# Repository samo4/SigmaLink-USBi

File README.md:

# SigmaLink USBi

The SigmaLink USBi is an all-in-one real-time programming interface.

## Testing

- [x] draws less than 500mA
- [ ] why female connector?
- [ ] _too little bulk capacitance on VBUS_ (100u at least)
- [ ] missing pullup on SDA
- [ ] wrong footprint 74LVC2G66
- [ ] wrong footprint B5819W SL
- [ ] Y1 has DNP?
- [ ] _missing pull up on I2C SDA line_
- [x] works with SigmaStudio aftter adding capacitance and pullup on SDA

## Original info

MAIN COORDINATOR: [Max Chan](https://github.com/xcvista)

The SigmaLink USBi is a low-budget real-time programming device for the freeDSP and other DSP boards from Analog Devices. It is a new PCB design based on a CY7C68013 chip.

It has the same features as the Analog Devices USB interface (EVAL-ADUSB2EBZ), such as changing parameters while already using the freeDSP or easy changes of the schematic in SigmaStudio. You also can write your program to the EEPROM.

Please refer to the documentation for more information:

[Google Doc](https://docs.google.com/document/d/13BDac6Mss2I0CBOsSrk4YG-c8GQUpgU41vkwsMnYBss/edit?usp=sharing)

## License

This work and all other materials under https://github.com/freeDSP are licensed under a [Creative Commons Attribution Share-Alike 4.0 license](LICENSE.md). This allows for both personal and commercial derivative works, as long as they credit freeDSP and release their designs under the same license.

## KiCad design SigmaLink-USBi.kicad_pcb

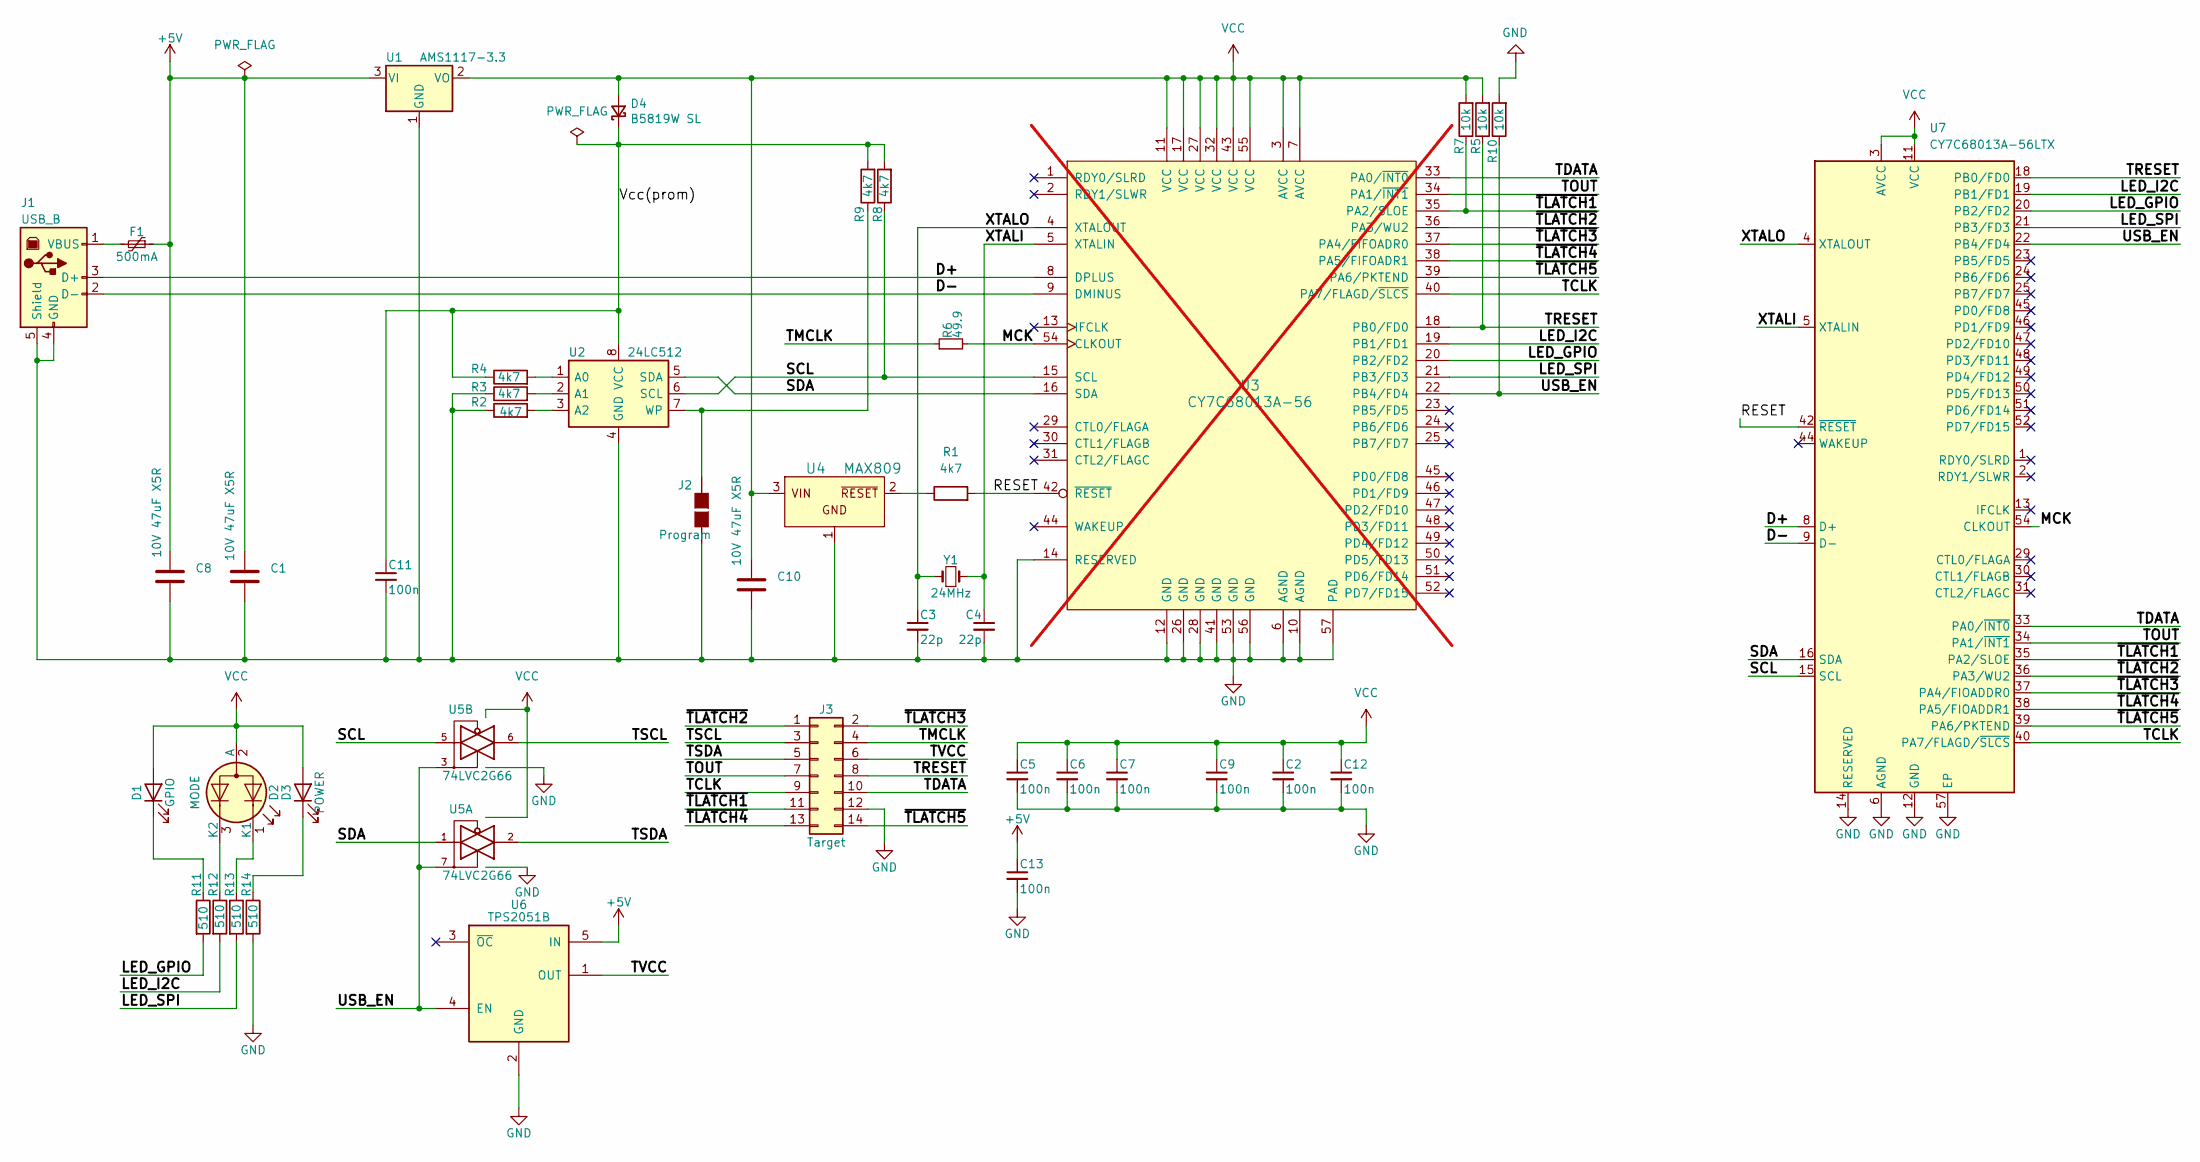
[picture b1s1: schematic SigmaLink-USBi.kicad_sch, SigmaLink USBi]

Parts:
C1, C8, C10: 10V 47uF X5R; C_1206_3216Metric; LCSC C96123
C2, C5, C6, C7, C9, C11, C12, C13: 100n; C_0402_1005Metric; LCSC C1525
C3, C4: 22p; C_0603_1608Metric; LCSC C1653
D1: GPIO; LED_D3.0mm; LCSC C86881
D2: MODE; LED_D3.0mm-3; LCSC C13559
D3: POWER; LED_D3.0mm; LCSC C85160
D4: B5819W SL; D_SOD-123; LCSC C8598
F1: 500mA; Fuse_1812_4532Metric_Pad1.30x3.40mm_HandSolder; LCSC C20979
J1: USB_B; USB_B_OST_USB-B1HSxx_Horizontal; LCSC C46392
J2: Program; PinHeader_1x02_P2.54mm_Vertical
J3: Target; IDC-Header_2x07_P2.54mm_Horizontal; LCSC C146622
R1, R2, R3, R4, R8, R9: 4k7; R_0402_1005Metric; LCSC C25900
R5, R7, R10: 10k; R_0402_1005Metric; LCSC C25744
R6: 49.9; R_0402_1005Metric
R11, R12, R13, R14: 510; R_0402_1005Metric; LCSC 0402
U1: AMS1117-3.3; SOT-223-3_TabPin2; LCSC C6186
U2: 24LC512; SOIC-8_3.9x4.9mm_P1.27mm; LCSC C6487
U3: CY7C68013A-56; QFN-56-1EP_8x8mm_P0.5mm_EP4.6x5.3mm; LCSC C14912; not fitted
U4: MAX809; SOT-23; LCSC C9965
U5: 74LVC2G66; VSSOP-8_3.0x3.0mm_P0.65mm; LCSC C181970
U6: TPS2051B; SOT-23-5; LCSC C24593
U7: CY7C68013A-56LTX; QFN-56-1EP_8x8mm_P0.5mm_EP4.5x5.2mm_ThermalVias_TopTented
Y1: 24MHz; Crystal_SMD_5032-2Pin_5.0x3.2mm; LCSC C122520

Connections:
+5V: C1.1, C8.1, C13.1, F1.1, U1.3 (VI), U6.5 (IN)
/D+: J1.3 (D+), U3.8 (DPLUS), U7.8 (D+)
/D-: J1.2 (D-), U3.9 (DMINUS), U7.9 (D-)
/LED_GPIO: R11.2, U3.20 (PB2/FD2), U7.20 (PB2/FD2)
/LED_I2C: R12.2, U3.19 (PB1/FD1), U7.19 (PB1/FD1)
/LED_SPI: R13.2, U3.21 (PB3/FD3), U7.21 (PB3/FD3)
/MCK: R6.2, U3.54 (CLKOUT), U7.54 (CLKOUT)
/RESET: R1.2, U3.42 (~RESET), U7.42 (~RESET)
/SCL: R8.1, U2.6 (SCL), U3.15 (SCL), U5.5, U7.15 (SCL)
/SDA: U2.5 (SDA), U3.16 (SDA), U5.1, U7.16 (SDA)
/TCLK: J3.9, U3.40 (PA7/FLAGD/~SLCS), U7.40 (PA7/FLAGD/~SLCS)
/TDATA: J3.10, U3.33 (PA0/~INT0), U7.33 (PA0/~INT0)
/TMCLK: J3.4, R6.1
/TOUT: J3.7, U3.34 (PA1/~INT1), U7.34 (PA1/~INT1)
/TRESET: J3.8, R5.1, U3.18 (PB0/FD0), U7.18 (PB0/FD0)
/TSCL: J3.3, U5.6
/TSDA: J3.5, U5.2
/TVCC: J3.6, U6.1 (OUT)
/USB_EN: R10.1, U3.22 (PB4/FD4), U5.3, U5.7, U6.4 (EN), U7.22 (PB4/FD4)
/Vcc(prom): C11.1, D4.1 (K), R4.1, R8.2, R9.2, U2.8 (VCC)
/XTALI: C4.1, U3.5 (XTALIN), U7.5 (XTALIN), Y1.2
/XTALO: C3.1, U3.4 (XTALOUT), U7.4 (XTALOUT), Y1.1
/~TLATCH1: J3.11, R7.1, U3.35 (PA2/SLOE), U7.35 (PA2/SLOE)
/~TLATCH2: J3.1, U3.36 (PA3/WU2), U7.36 (PA3/WU2)
/~TLATCH3: J3.2, U3.37 (PA4/FIFOADR0), U7.37 (PA4/FIOADDR0)
/~TLATCH4: J3.13, U3.38 (PA5/FIFOADR1), U7.38 (PA5/FIOADDR1)
/~TLATCH5: J3.14, U3.39 (PA6/PKTEND), U7.39 (PA6/PKTEND)
GND: C1.2, C2.2, C3.2, C4.2, C5.2, C6.2, C7.2, C8.2, C9.2, C10.2, C11.2, C12.2, C13.2, J1.4 (GND), J1.5 (Shield), J2.2 (G2), J3.12, R2.1, R3.1, R10.2, R14.2, U1.1 (GND), U2.4 (GND), U3.6 (AGND), U3.10 (AGND), U3.12 (GND), U3.14 (RESERVED), U3.26 (GND), U3.28 (GND), U3.41 (GND), U3.53 (GND), U3.56 (GND), U3.57 (PAD), U4.1 (GND), U5.4 (GND), U6.2 (GND), U7.6 (AGND), U7.10 (AGND), U7.12 (GND), U7.14 (RESERVED), U7.26 (GND), U7.28 (GND), U7.41 (GND), U7.53 (GND), U7.56 (GND), U7.57 (EP)
unnamed: D1.1 (K), R11.1
unnamed: D2.1 (K1), R13.1
unnamed: D2.3 (K2), R12.1
unnamed: D3.1 (K), R14.1
unnamed: F1.2, J1.1 (VBUS)
unnamed: J2.1 (G1), R9.1, U2.7 (WP)
unnamed: R4.2, U2.1 (A0)
unnamed: R3.2, U2.2 (A1)
unnamed: R2.2, U2.3 (A2)
unnamed: R1.1, U4.2 (~RESET)
VCC: C2.1, C5.1, C6.1, C7.1, C9.1, C10.1, C12.1, D1.2 (A), D2.2 (A), D3.2 (A), D4.2 (A), R5.2, R7.2, U1.2 (VO), U3.3 (AVCC), U3.7 (AVCC), U3.11 (VCC), U3.17 (VCC), U3.27 (VCC), U3.32 (VCC), U3.43 (VCC), U3.55 (VCC), U4.3 (VIN), U5.8 (VCC), U7.3 (AVCC), U7.7 (AVCC), U7.11 (VCC), U7.17 (VCC), U7.27 (VCC), U7.32 (VCC), U7.43 (VCC), U7.55 (VCC)

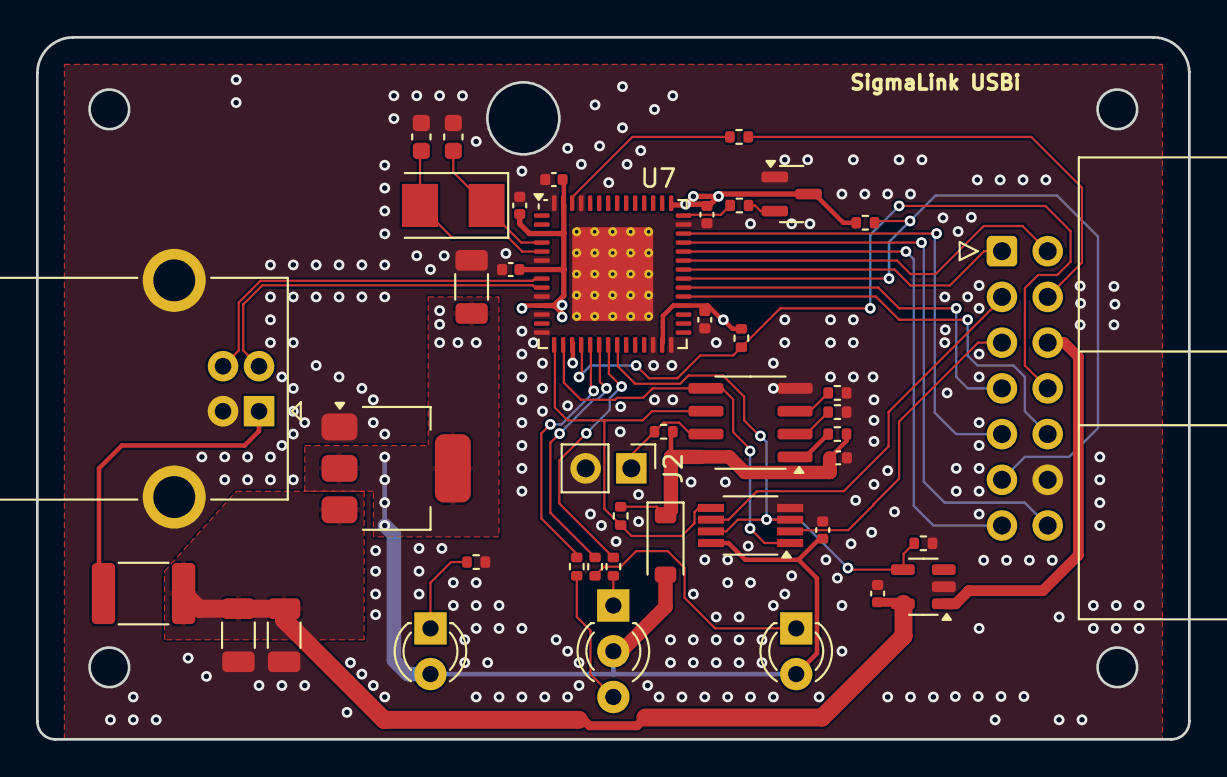
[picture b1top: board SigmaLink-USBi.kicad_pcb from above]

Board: 2 copper layers, 64.0 x 39.0 mm, 42 parts (0 on the bottom side), 39 nets.

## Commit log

2024-06-29 refactoring, move to 8.0
2024-08-13 gerbers
2024-10-07 ordered
2025-04-21 testing
